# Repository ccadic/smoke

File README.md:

# smoke
SmokeEvacuator Diagrams
Dr CADIC Philippe

Medical Laser Smoke evacuator project
It is opensource

3D files to 3D print
Kicad files and gerber

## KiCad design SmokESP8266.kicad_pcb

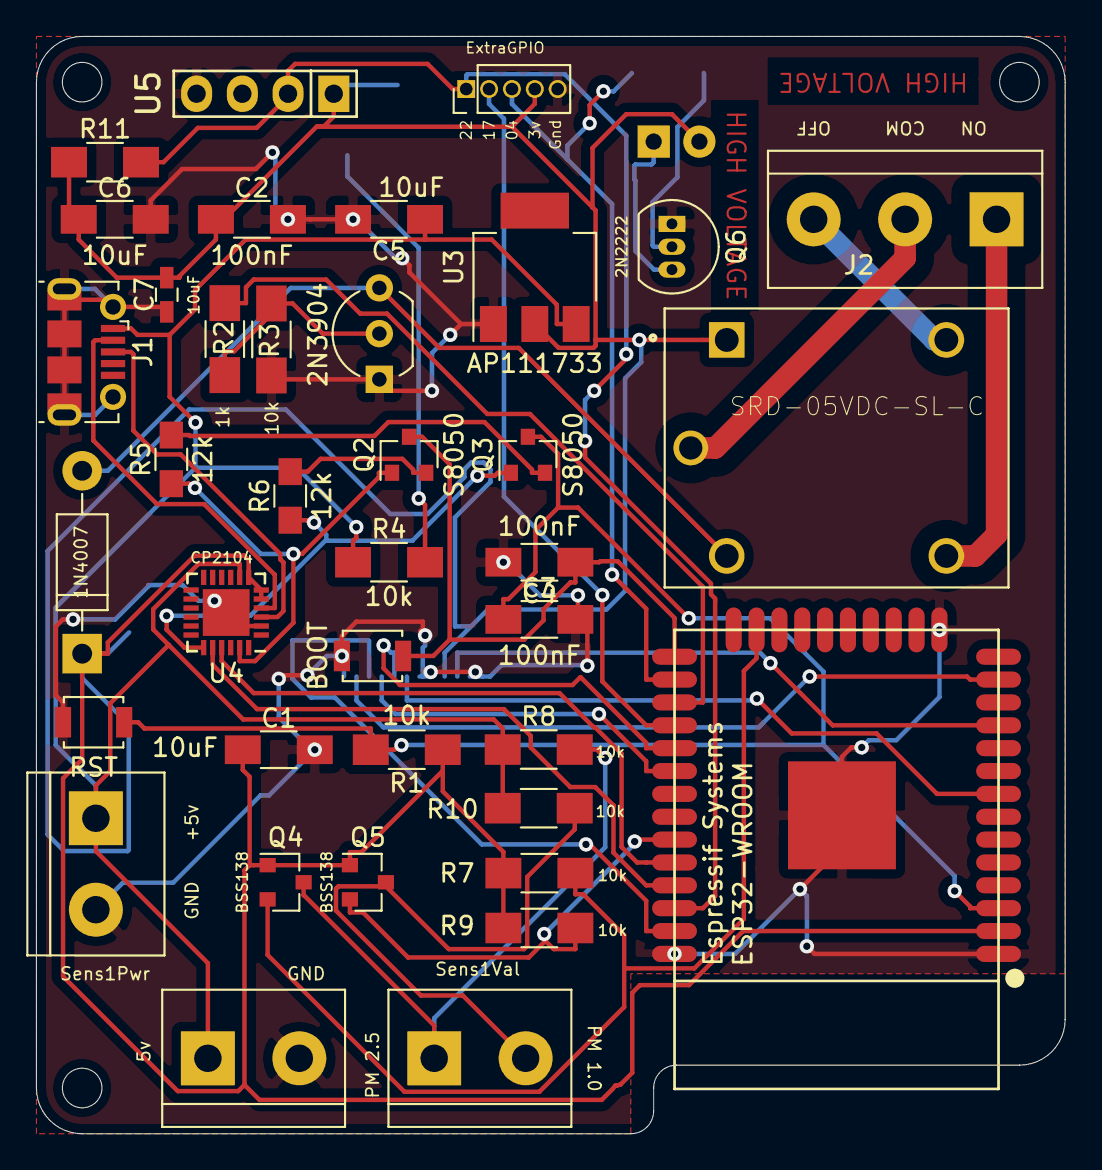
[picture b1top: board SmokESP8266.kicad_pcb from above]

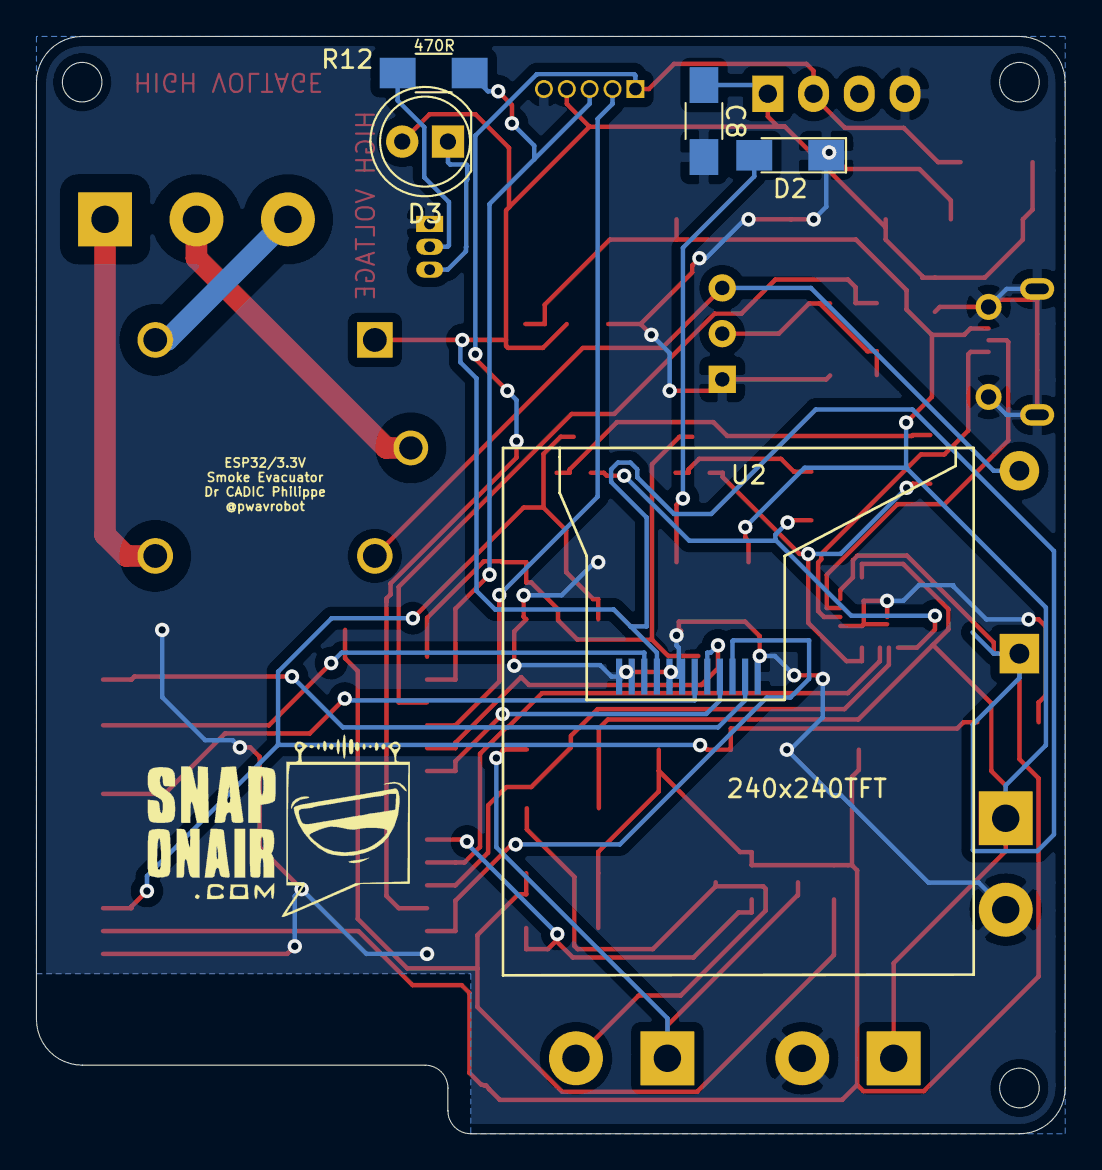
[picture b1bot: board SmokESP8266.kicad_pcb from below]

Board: 2 copper layers, 57.2 x 61.0 mm, 46 parts (5 on the bottom side), 35 nets.

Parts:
C1, C5, C6: 10uF; C_1206_HandSoldering
C2, C3, C4, C8: 100nF; C_1206_HandSoldering
C7: 10uF; C_0603_HandSoldering
D1: 1N4007; D_DO-41_SOD81_P10.16mm_Horizontal
D2: PowerOn; LED_1206_HandSoldering
D3: IR-LED; LED_D5.0mm_FlatTop
H1, H2, H3: MountingHole; MountingHole_2.2mm_M2
J1: USB_OTG; USB_Micro-B_Molex-105017-0001
J2: Cnctor; TerminalBlock_bornier-3_P5.08mm
J3: Sens1Val; TerminalBlock_bornier-2_P5.08mm
J4: Sens1Pwr; TerminalBlock_bornier-2_P5.08mm
J5: ExtraGPIO; Socket_Strip_Straight_1x05_Pitch1.27mm
J6: ALIMCapt; TerminalBlock_bornier-2_P5.08mm
K1: SRD-05VDC-SL-C; RELAY_SRD-05VDC-SL-C
Q1: 2N3904; TO-92_Inline_Wide
Q2, Q3: S8050; SOT-23
Q4, Q5: BSS138; SOT-23
Q6: 2N2222; TO-92_Inline_Narrow_Oval
R1, R3, R4, R7, R8, R9, R10: 10k; R_1206_HandSoldering
R2: 1k; R_1206_HandSoldering
R5, R6: 12k; R_0805_HandSoldering
R11: 4.7k; R_1206_HandSoldering
R12: 470R; R_1206_HandSoldering
SW1: RST; SW_SPST_B3U-1000P
SW2: BOOT; SW_SPST_B3U-1000P
U1: ESP32-WROOM
U2: 240x240TFT; 240240TFT
U3: AP111733; SOT-223
U4: CP2104; QFN-24-1EP_4x4mm_Pitch0.5mm
U5: DHT11; DHT11-debout

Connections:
+3V3: C1.1, C2.1, C6.1, C7.2, C8.1, D1.1, D3.2, J5.4, K1.1, Q4.1, Q5.1, R1.1, R7.1, R9.1, R11.1, U1.2, U2.4, U3.2, U4.5, U4.6, U4.7, U5.1
+5V: C5.1, J1.1, J4.1, J6.1, R4.1, R8.1, R10.1, U3.3, U4.8
/3vPM1: Q5.2, R9.2, U1.33
/3vPM25: Q4.2, R7.2, U1.23
/5vPM1: J3.2, Q5.3, R10.2
/5vPM25: J3.1, Q4.3, R8.2
/Bootb: C4.1, Q2.3, SW2.2, U1.25
/CLK: U1.30, U2.9
/D+: J1.3, U4.3
/D-: J1.2, U4.4
/DCDISP: U1.8, U2.7
/DTR: Q2.1, R5.1, U4.23
/GPIO4: J5.3, R12.2, U1.26
/IO16: R2.2, U1.27
/IO17: J5.2, U1.28
/IO22: J5.1, R11.2, U1.36, U5.2
/LEDA: U1.11, U2.3
/MOSI: U1.37, U2.10
/RESETB: C3.1, Q3.3, R1.2, SW1.2, U1.3
/RESETDISP: U1.13, U2.11
/RTS: Q3.1, R6.1, U4.19
/RXD0: U1.34, U4.21
/SPI_SS: U1.29, U2.8
/TXD0: U1.35, U4.20
GND: C1.2, C2.2, C3.2, C4.2, C5.2, C6.2, C7.1, C8.2, D2.1, J1.5, J1.6, J4.2, J5.5, J6.2, Q1.1, Q6.1, R3.1, SW1.1, SW2.1, U1.1, U1.15, U1.38, U1.39, U2.1, U2.2, U2.5, U2.6, U2.12, U3.1, U4.2, U4.25, U5.4
unnamed: D1.2, K1.4, Q1.3
unnamed: D2.2, R4.2
unnamed: D3.1, Q6.3
unnamed: J2.1, K1.3
unnamed: J2.2, K1.5
unnamed: J2.3, K1.2
unnamed: Q1.2, R2.1, R3.2
unnamed: Q2.2, R6.2
unnamed: Q3.2, R5.2
unnamed: Q6.2, R12.1
